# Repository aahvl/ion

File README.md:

# ION

Hi! I am Aahil, And I made Ion!

Ion(Pad) is a multi usage macropad that will have a selector wheel, customizable keys, and even more along the way.

## How will you use the IonPad?
You press the keys for Copy, paste, cut, and the knob for volume control! (this is what it does now.)
Soon it will have a nice software and faster click times for Geometry Dash, Osu and even more!

Also, All these features except from the "Copy, Paste, Cut, Volume Controls" work in my example firmware, but I will do the rest of the features when the parts come.
And then, "you still didn't use the selector wheel, do you mean the rotary knob is for then you should fix it - @PenguinMo"  Selector Wheel is gonna be a overlay UI coming out after I get the parts to make and test it out, and that is what the rotary knob will be used for after i recieve the parts, but as for now, its a Volume Control.

## Why did I make this?
I want to help other people make a macropad, so I made this so other people can base off this project, and especially the software.

p.s reviewers heres the cad onshape link: [here](https://cad.onshape.com/documents/6712e51ebf114c6a4c189719/w/483d595bdc89a78519b30786/e/276eeeabe244c6235e0d0a11?renderMode=0&uiState=699f2c64c889dd3bfd28ac00)

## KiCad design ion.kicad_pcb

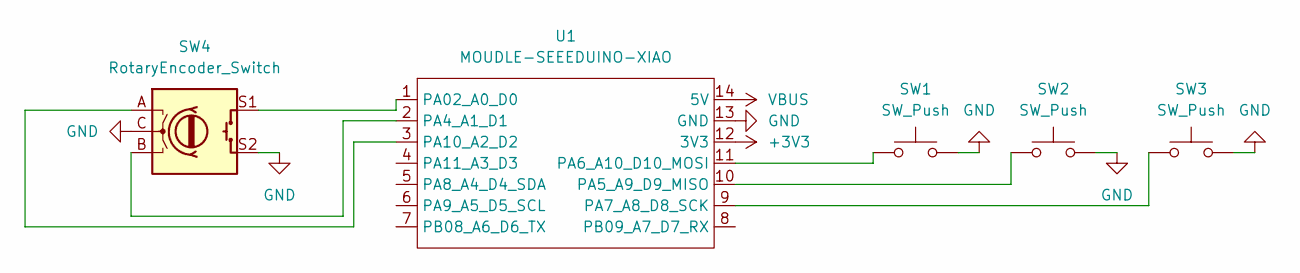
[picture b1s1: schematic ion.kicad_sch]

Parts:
SW1, SW2, SW3: SW_Push; SW_Cherry_MX_1.00u_PCB
SW4: RotaryEncoder_Switch; RotaryEncoder_Alps_EC11E-Switch_Vertical_H20mm
U1: MOUDLE-SEEEDUINO-XIAO; XIAO-Generic-Hybrid-14P-2.54-21X17.8MM

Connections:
+3V3: U1.12 (3V3)
GND: SW1.2, SW2.2, SW3.2, SW4.C, SW4.S2, U1.13 (GND)
unnamed: SW4.S1, U1.1 (PA02_A0_D0)
unnamed: SW4.B, U1.2 (PA4_A1_D1)
unnamed: SW2.1, U1.10 (PA5_A9_D9_MISO)
unnamed: SW1.1, U1.11 (PA6_A10_D10_MOSI)
unnamed: SW3.1, U1.9 (PA7_A8_D8_SCK)
unnamed: SW4.A, U1.3 (PA10_A2_D2)
VBUS: U1.14 (5V)

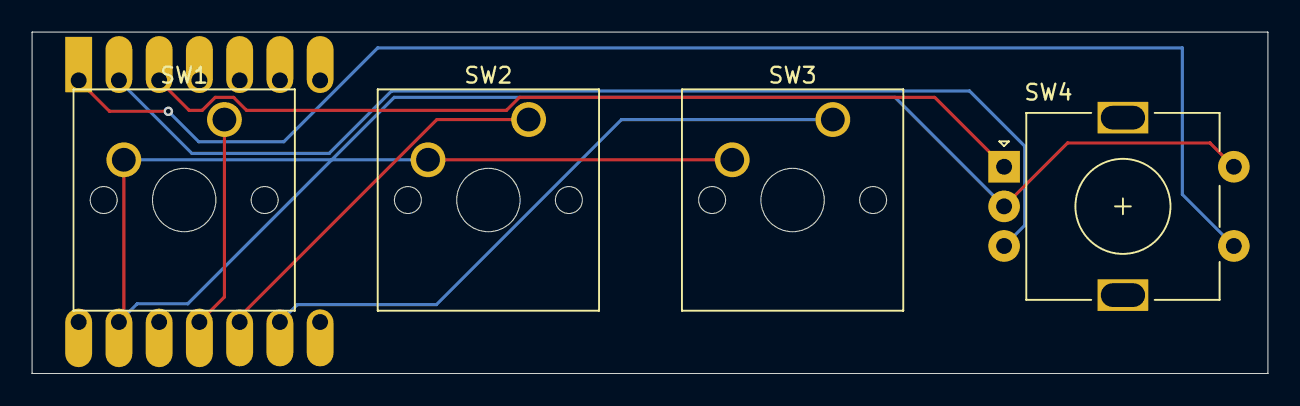
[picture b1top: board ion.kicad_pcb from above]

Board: 2 copper layers, 78.0 x 21.6 mm, 5 parts (1 on the bottom side), 7 nets.

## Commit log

2026-02-23 ion pcb
2026-02-23 Create hardware
2026-02-23 PCB Files
2026-02-23 Create placeholder
